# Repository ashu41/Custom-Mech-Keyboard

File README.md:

# Custom-Mech-Keyboard
Builiding a 65% layout keyboard from scratch

Purchase links:

OLED display: 
----------------------Need to check compatible QMK drivers------------------------------------------
1. https://robu.in/product/0-91-inch-128x32-i2c-iic-serial-oled-lcd-display-modulewith-gnd-vcc-white/
2. https://robu.in/product/waveshare-128x32-general-0-91inch-oled-display-module/
3. https://robu.in/product/0-91-inch-128x32-i2c-iic-serial-blue-oled-lcd-display-module/
4. https://robu.in/product/waveshare-pico-1-3-inch-oled-display-module/

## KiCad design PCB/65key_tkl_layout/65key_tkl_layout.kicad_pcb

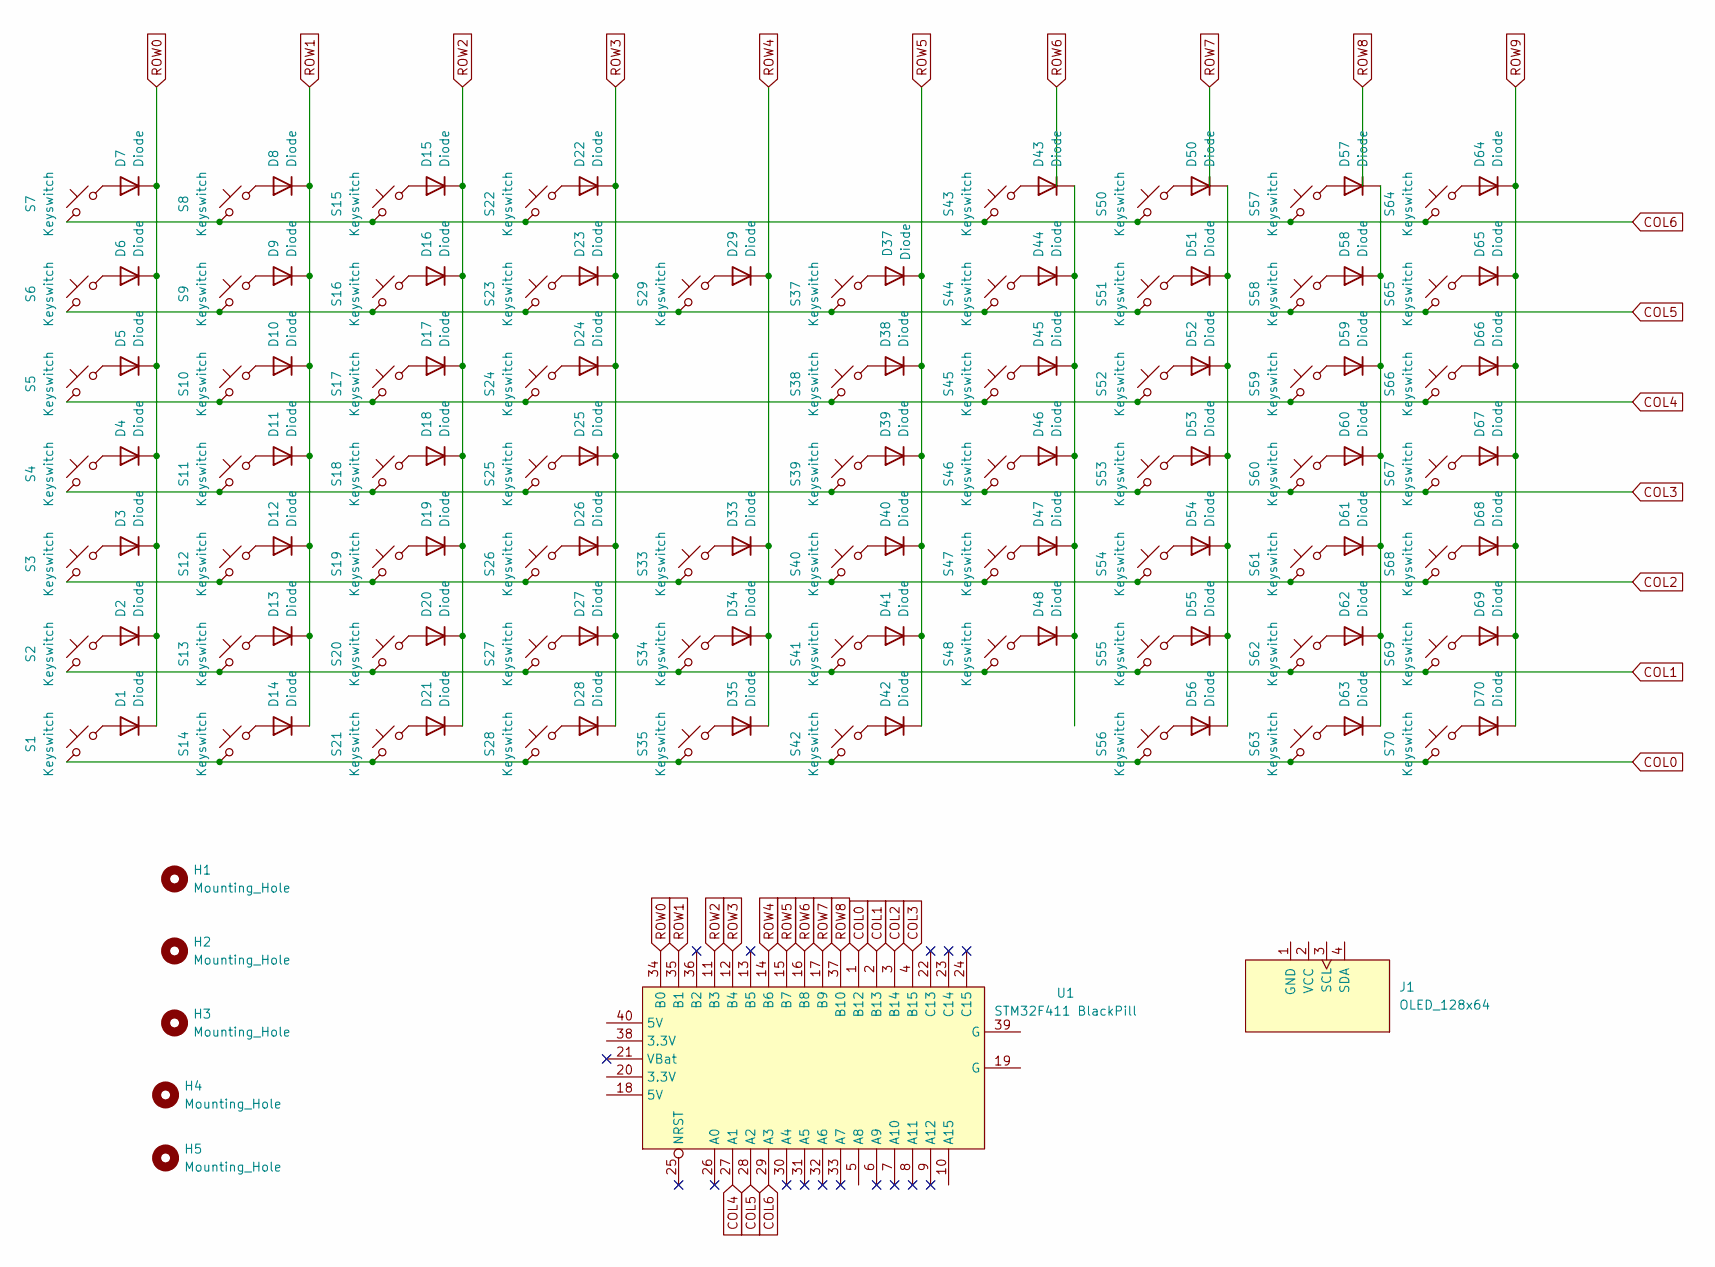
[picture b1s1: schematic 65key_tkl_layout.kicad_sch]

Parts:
D1, D2, D3, D4, D5, D6, D7, D8, D9, D10, D11, D12, D13, D14, D15, D16, D17, D18, D19, D20, D21, D22, D23, D24, D25, D26, D27, D28, D29, D33, D34, D35, D37, D38, D39, D40, D41, D42, D43, D44, D45, D46, D47, D48, D50, D51, D52, D53, D54, D55, D56, D57, D58, D59, D60, D61, D62, D63, D64, D65, D66, D67, D68, D69, D70: Diode; Diode_SOD-123
H1, H2, H3, H4: Mounting_Hole; Stabilizer_MX_2.00u
H5: Mounting_Hole; Stabilizer_MX_6.25u
J1: OLED_128x64
S1, S2, S3, S4, S5, S6, S7, S8, S9, S10, S11, S12, S13, S15, S16, S17, S18, S19, S20, S22, S23, S24, S25, S26, S27, S37, S38, S39, S40, S41, S42, S43, S44, S45, S46, S48, S50, S51, S52, S53, S54, S56, S57, S58, S59, S60, S61, S62, S64, S65, S66, S67, S68, S69: Keyswitch; Hotswap_MX_1.00u
S14, S63: Keyswitch; Hotswap_MX_1.50u
S21, S47: Keyswitch; Hotswap_MX_1.75u
S28, S55: Keyswitch; Hotswap_MX_2.25u
S29: Keyswitch; Hotswap_MX_6.25u
S33, S34, S35: Keyswitch; Hotswap_MX_1.25u
S70: Keyswitch; Hotswap_MX_2.00u
U1: STM32F411 BlackPill; STM32F411_Black_Pill

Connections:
COL0: S1.1, S14.1, S21.1, S28.1, S35.1, S42.1, S56.1, S63.1, S70.1, U1.1 (B12)
COL1: S2.1, S13.1, S20.1, S27.1, S34.1, S41.1, S48.1, S55.1, S62.1, S69.1, U1.2 (B13)
COL2: S3.1, S12.1, S19.1, S26.1, S33.1, S40.1, S47.1, S54.1, S61.1, S68.1, U1.3 (B14)
COL3: S4.1, S11.1, S18.1, S25.1, S39.1, S46.1, S53.1, S60.1, S67.1, U1.4 (B15)
COL4: S5.1, S10.1, S17.1, S24.1, S38.1, S45.1, S52.1, S59.1, S66.1, U1.27 (A1)
COL5: S6.1, S9.1, S16.1, S23.1, S29.1, S37.1, S44.1, S51.1, S58.1, S65.1, U1.28 (A2)
COL6: S7.1, S8.1, S15.1, S22.1, S43.1, S50.1, S57.1, S64.1, U1.29 (A3)
unnamed: D1.2 (A), S1.2
unnamed: D2.2 (A), S2.2
unnamed: D3.2 (A), S3.2
unnamed: D4.2 (A), S4.2
unnamed: D5.2 (A), S5.2
unnamed: D6.2 (A), S6.2
unnamed: D7.2 (A), S7.2
unnamed: D8.2 (A), S8.2
unnamed: D9.2 (A), S9.2
unnamed: D10.2 (A), S10.2
unnamed: D11.2 (A), S11.2
unnamed: D12.2 (A), S12.2
unnamed: D13.2 (A), S13.2
unnamed: D14.2 (A), S14.2
unnamed: D15.2 (A), S15.2
unnamed: D16.2 (A), S16.2
unnamed: D17.2 (A), S17.2
unnamed: D18.2 (A), S18.2
unnamed: D19.2 (A), S19.2
unnamed: D20.2 (A), S20.2
unnamed: D21.2 (A), S21.2
unnamed: D22.2 (A), S22.2
unnamed: D23.2 (A), S23.2
unnamed: D24.2 (A), S24.2
unnamed: D25.2 (A), S25.2
unnamed: D26.2 (A), S26.2
unnamed: D27.2 (A), S27.2
unnamed: D28.2 (A), S28.2
unnamed: D29.2 (A), S29.2
unnamed: D33.2 (A), S33.2
unnamed: D34.2 (A), S34.2
unnamed: D35.2 (A), S35.2
unnamed: D37.2 (A), S37.2
unnamed: D38.2 (A), S38.2
unnamed: D39.2 (A), S39.2
unnamed: D40.2 (A), S40.2
unnamed: D41.2 (A), S41.2
unnamed: D42.2 (A), S42.2
unnamed: D43.2 (A), S43.2
unnamed: D43.1 (K), D44.1 (K), D45.1 (K), D46.1 (K), D47.1 (K), D48.1 (K)
unnamed: D44.2 (A), S44.2
unnamed: D45.2 (A), S45.2
unnamed: D46.2 (A), S46.2
unnamed: D47.2 (A), S47.2
unnamed: D48.2 (A), S48.2
unnamed: D50.2 (A), S50.2
unnamed: D50.1 (K), D51.1 (K), D52.1 (K), D53.1 (K), D54.1 (K), D55.1 (K), D56.1 (K)
unnamed: D51.2 (A), S51.2
unnamed: D52.2 (A), S52.2
unnamed: D53.2 (A), S53.2
unnamed: D54.2 (A), S54.2
unnamed: D55.2 (A), S55.2
unnamed: D56.2 (A), S56.2
unnamed: D57.2 (A), S57.2
unnamed: D57.1 (K), D58.1 (K), D59.1 (K), D60.1 (K), D61.1 (K), D62.1 (K), D63.1 (K)
unnamed: D58.2 (A), S58.2
unnamed: D59.2 (A), S59.2
unnamed: D60.2 (A), S60.2
unnamed: D61.2 (A), S61.2
unnamed: D62.2 (A), S62.2
unnamed: D63.2 (A), S63.2
unnamed: D64.2 (A), S64.2
unnamed: D65.2 (A), S65.2
unnamed: D66.2 (A), S66.2
unnamed: D67.2 (A), S67.2
unnamed: D68.2 (A), S68.2
unnamed: D69.2 (A), S69.2
unnamed: D70.2 (A), S70.2
ROW0: D1.1 (K), D2.1 (K), D3.1 (K), D4.1 (K), D5.1 (K), D6.1 (K), D7.1 (K), U1.34 (B0)
ROW1: D8.1 (K), D9.1 (K), D10.1 (K), D11.1 (K), D12.1 (K), D13.1 (K), D14.1 (K), U1.35 (B1)
ROW2: D15.1 (K), D16.1 (K), D17.1 (K), D18.1 (K), D19.1 (K), D20.1 (K), D21.1 (K), U1.11 (B3)
ROW3: D22.1 (K), D23.1 (K), D24.1 (K), D25.1 (K), D26.1 (K), D27.1 (K), D28.1 (K), U1.12 (B4)
ROW4: D29.1 (K), D33.1 (K), D34.1 (K), D35.1 (K), U1.14 (B6)
ROW5: D37.1 (K), D38.1 (K), D39.1 (K), D40.1 (K), D41.1 (K), D42.1 (K), U1.15 (B7)
ROW6: U1.16 (B8)
ROW7: U1.17 (B9)
ROW8: U1.37 (B10)
ROW9: D64.1 (K), D65.1 (K), D66.1 (K), D67.1 (K), D68.1 (K), D69.1 (K), D70.1 (K)

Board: 2 copper layers, 137 parts (0 on the bottom side), 82 nets, no tracks yet.

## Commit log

2024-09-06 Created test files
2024-09-06 Libraries added
2024-09-06 libraries synced
2024-09-12 PCB design and added references
